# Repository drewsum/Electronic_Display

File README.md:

# Electronic_Display
320x256 LED Display, Marquette Senior Design Project2018-2019, Team E44

20 64x64 HUB75E LED Panels strung together in a 5x4 arrangement, controlled by a PIC32MZ MCU on a host board, alongside an android app

Microconctroller U601 on logic PCB is programmed with firmware in sfw/embedded_firmware/U601_Firmware with PICKIT 3

Two PCBs reside in hdw, designed in KiCad v5.1.0. Both projects require schematic symbols and footprint libraries located in hdw/lib

Embedded firmware resides in sfw/embedded_firmware, built with XC32 v21.0 w/ Pro license (-O2 omptimization level) with MPLabX v5.15

Android app resides in sfw/app/LED_Display, built with Android Studio API level 26

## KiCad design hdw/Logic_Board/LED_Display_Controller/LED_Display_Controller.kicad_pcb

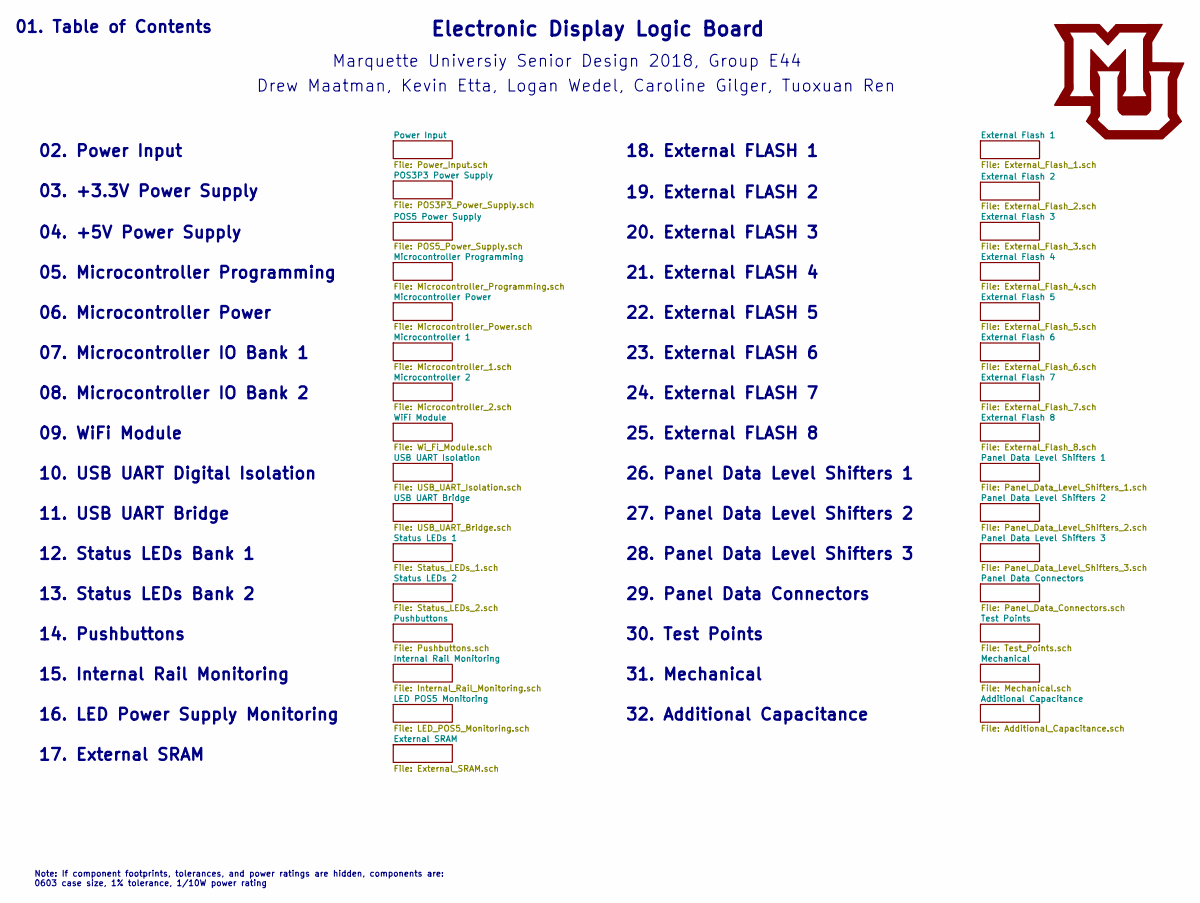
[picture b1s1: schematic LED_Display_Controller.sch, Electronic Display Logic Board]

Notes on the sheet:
02. Power Input
03. +3.3V Power Supply
04. +5V Power Supply
05. Microcontroller Programming
06. Microcontroller Power
07. Microcontroller IO Bank 1
08. Microcontroller IO Bank 2
09. WiFi Module
10. USB UART Digital Isolation
11. USB UART Bridge
12. Status LEDs Bank 1
13. Status LEDs Bank 2
14. Pushbuttons
15. Internal Rail Monitoring
16. LED Power Supply Monitoring
17. External SRAM
18. External FLASH 1
19. External FLASH 2
20. External FLASH 3
21. External FLASH 4
22. External FLASH 5
23. External FLASH 6
24. External FLASH 7
25. External FLASH 8
26. Panel Data Level Shifters 1
27. Panel Data Level Shifters 2
28. Panel Data Level Shifters 3
29. Panel Data Connectors
30. Test Points
31. Mechanical
Electronic Display Logic Board
Marquette Universiy Senior Design 2018, Group E44
Drew Maatman, Kevin Etta, Logan Wedel, Caroline Gilger, Tuoxuan Ren
01. Table of Contents
Note: If component footprints, tolerances, and power ratings are hidden, components are: 0603 case size, 1% tolerance, 1/10W power rating
32. Additional Capacitance

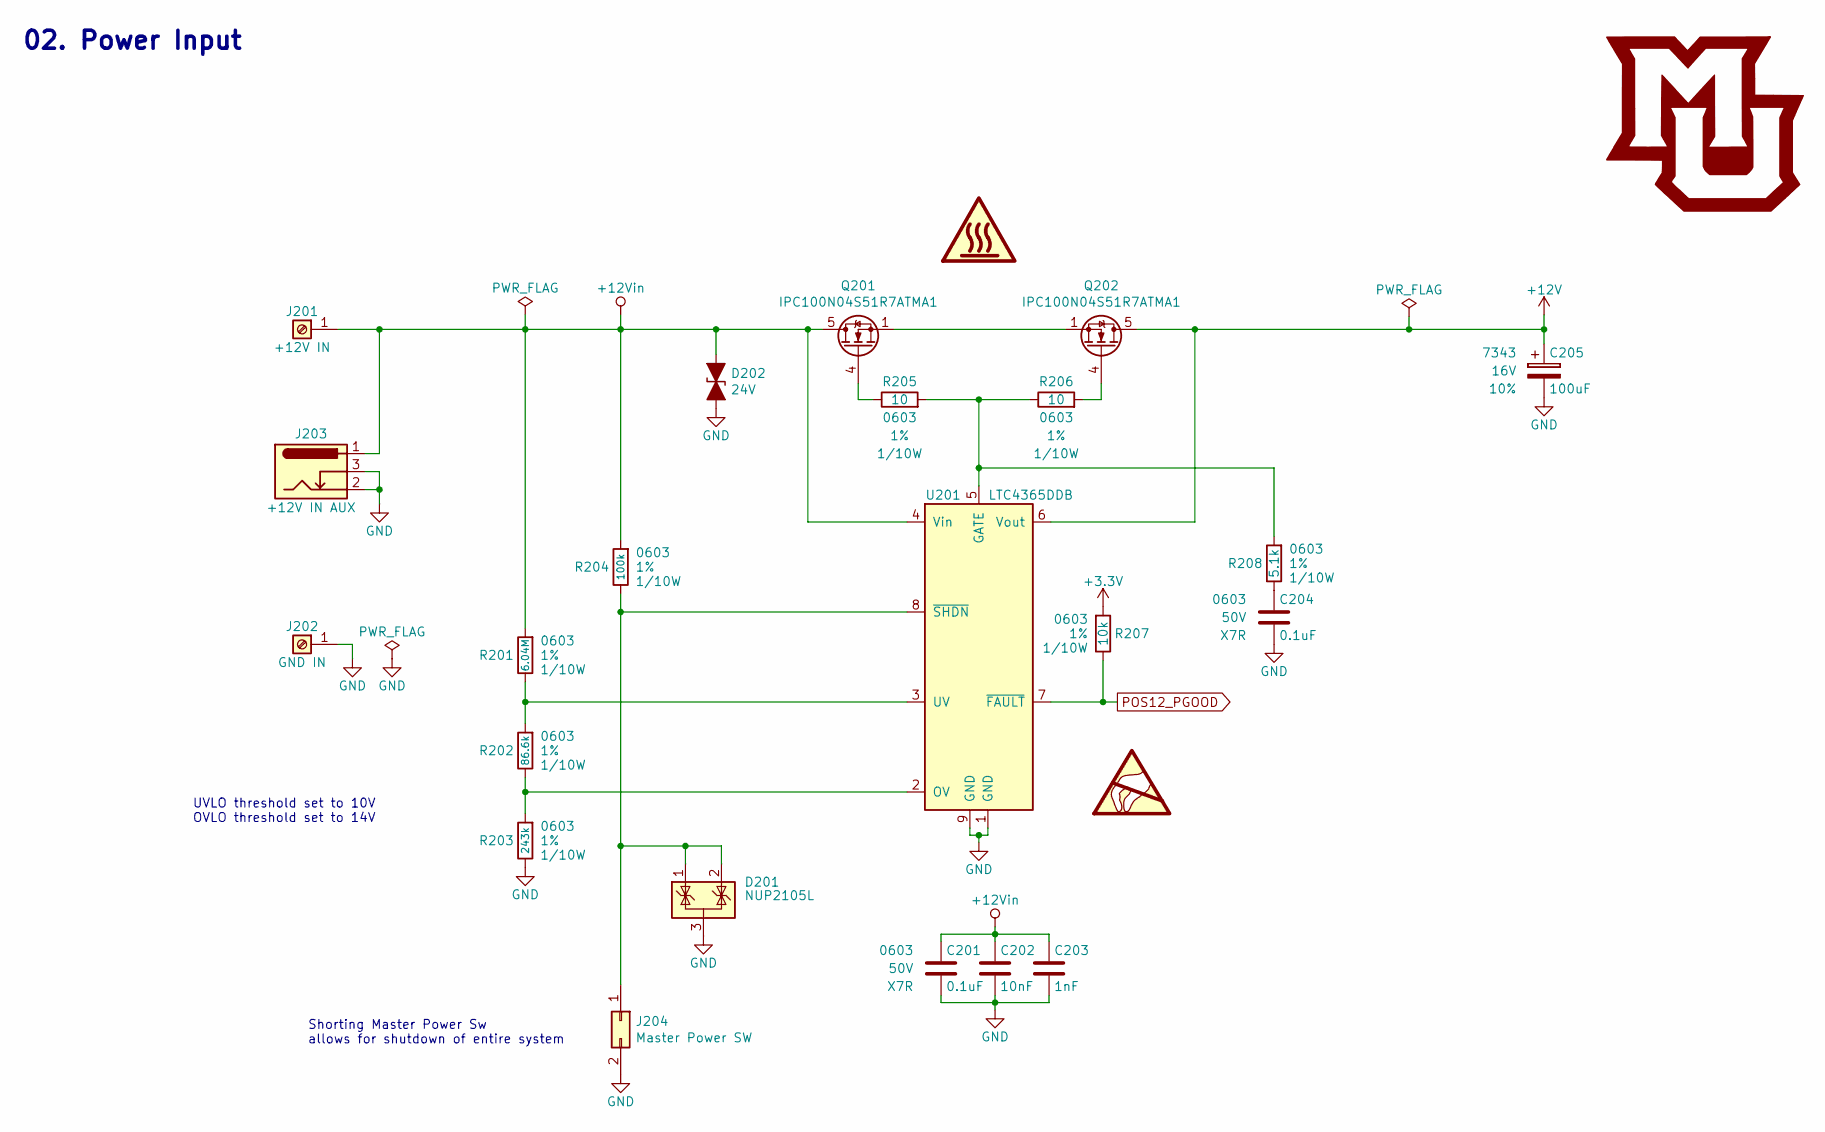
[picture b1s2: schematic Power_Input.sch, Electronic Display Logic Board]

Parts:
C201, C204: 0.1uF; C_0603; Voltage 50V; Digi-Key PN 311-1344-1-ND
C202: 10nF; C_0603; Voltage 50V; Digi-Key PN 1276-1921-1-ND
C203: 1nF; C_0603; Voltage 50V; Digi-Key PN 1276-1018-1-ND
C205: 100uF; CP_Tantalum_Case-X_EIA-7343-43_Reflow; Voltage 16V; Tolerance 10%; Digi-Key PN 718-1102-1-ND
D201: NUP2105L; SOT-23; Digi-Key PN NUP2105LT1GOSCT-ND
D202: 24V; D_SMA; Digi-Key PN SMAJ24CALFCT-ND
J201: +12V IN; Wuerth_7461096_M4_Shank_9pos; Digi-Key PN 732-3214-ND
J202: GND IN; Wuerth_7461096_M4_Shank_9pos; Digi-Key PN 732-3214-ND
J203: +12V IN AUX; BARREL_JACK; Digi-Key PN CP-202BH-ND
J204: Master Power SW; Pin_Header_Straight_1x02_Pitch2.54mm
Q201, Q202: IPC100N04S51R7ATMA1; TDSON-8-1; Digi-Key PN IPC100N04S51R7ATMA1CT-ND
R201: 6.04M; R_0603; Tolerance 1%; Digi-Key PN 541-6.04MHCT-ND
R202: 86.6k; R_0603; Tolerance 1%; Digi-Key PN 311-86.6KHRCT-ND
R203: 243k; R_0603; Tolerance 1%; Digi-Key PN 311-243KHRCT-ND
R204: 100k; R_0603; Tolerance 1%; Digi-Key PN A106046CT-ND
R205, R206: 10; R_0603; Tolerance 1%; Digi-Key PN YAG3351CT-ND
R207: 10k; R_0603; Tolerance 1%; Digi-Key PN RMCF0603FT10K0CT-ND
R208: 5.1k; R_0603; Tolerance 1%; Digi-Key PN YAG3621CT-ND
U201: LTC4365DDB; DFN-8-1EP_2x3mm_Pitch0.5mm; Digi-Key PN LTC4365IDDB#TRMPBFCT-ND

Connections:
+3V3: R207.1; also elsewhere on the board
+12V: C205.1, Q202.5 (D), U201.6 (Vout); also elsewhere on the board
+12Vin: C201.1, C202.1, C203.1, D202.1 (A1), J201.1, J203.1, Q201.5 (D), R201.1, R204.1, U201.4 (Vin); also elsewhere on the board
GND: C201.2, C202.2, C203.2, C204.2, C205.2, D201.3 (A), D202.2 (A2), J202.1, J203.2, J203.3, J204.2, R203.2, U201.1 (GND), U201.9 (GND); also elsewhere on the board
unnamed: C204.1, R208.2
unnamed: D201.1 (K), D201.2 (K), J204.1, R204.2, U201.8 (~SHDN)
unnamed: Q201.1 (S), Q201.2 (S), Q201.3 (S), Q202.1 (S), Q202.2 (S), Q202.3 (S)
unnamed: Q201.4 (G), R205.2
unnamed: Q202.4 (G), R206.1
unnamed: R201.2, R202.1, U201.3 (UV)
unnamed: R202.2, R203.1, U201.2 (OV)
unnamed: R205.1, R206.2, R208.1, U201.5 (GATE)
POS12_PGOOD: R207.2, U201.7 (~FAULT); also elsewhere on the board

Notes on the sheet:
UVLO threshold set to 10V OVLO threshold set to 14V
Shorting Master Power Sw allows for shutdown of entire system
02. Power Input

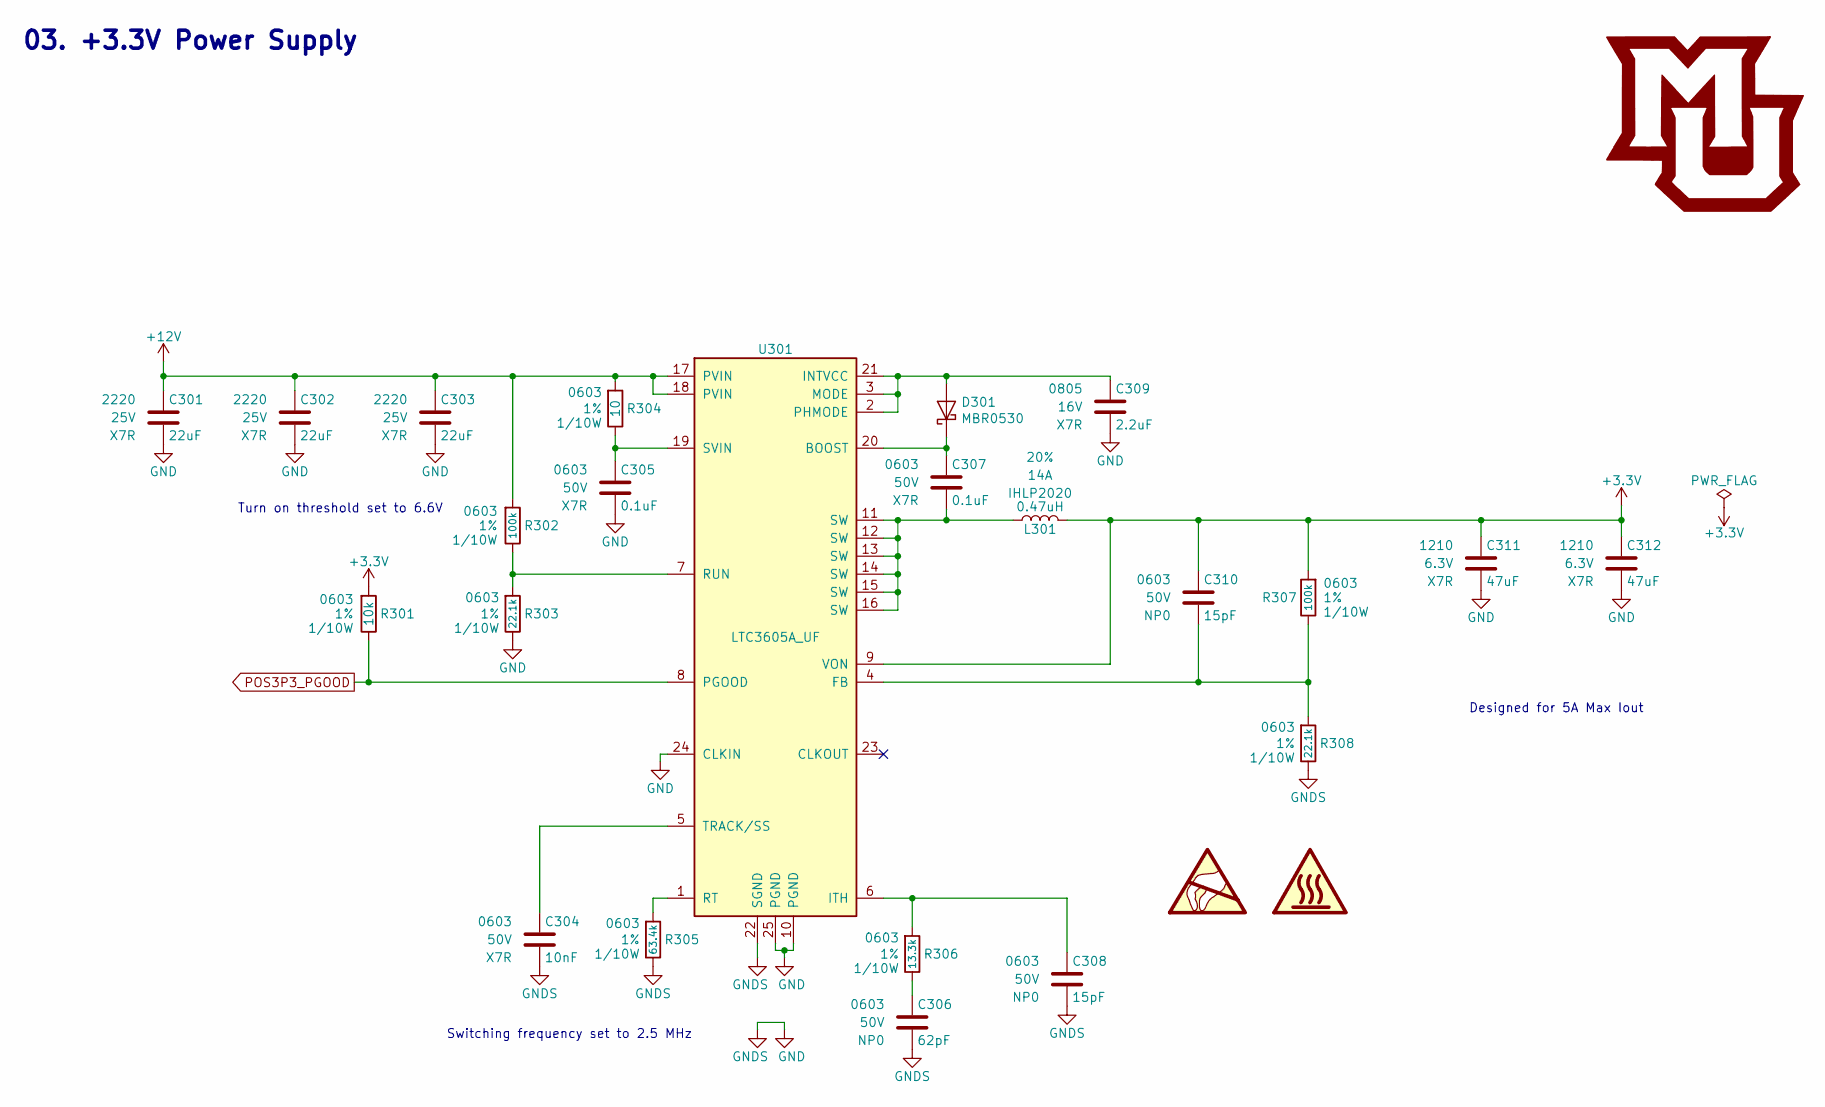
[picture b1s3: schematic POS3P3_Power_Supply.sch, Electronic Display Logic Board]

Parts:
C301, C302, C303: 22uF; C_2220; Voltage 25V; Digi-Key PN 445-1453-1-ND
C304: 10nF; C_0603; Voltage 50V; Digi-Key PN 1276-1921-1-ND
C305, C307: 0.1uF; C_0603; Voltage 50V; Digi-Key PN 311-1344-1-ND
C306: 62pF; C_0603; Voltage 50V; Digi-Key PN 1276-2320-1-ND
C308, C310: 15pF; C_0603; Voltage 50V; Digi-Key PN 478-10289-1-ND
C309: 2.2uF; C_0805; Voltage 16V; Digi-Key PN 445-5691-1-ND
C311, C312: 47uF; C_1210; Voltage 6.3V; Digi-Key PN 490-4844-1-ND
D301: MBR0530; D_SOD-123; Digi-Key PN MBR0530T1GOSCT-ND
L301: 0.47uH; L_Vishay_IHLP-2020; Tolerance 20%; Digi-Key PN 541-1231-1-ND
R301: 10k; R_0603; Tolerance 1%; Digi-Key PN RMCF0603FT10K0CT-ND
R302, R307: 100k; R_0603; Tolerance 1%; Digi-Key PN A106046CT-ND
R303, R308: 22.1k; R_0603; Tolerance 1%; Digi-Key PN P22.1KHCT-ND
R304: 10; R_0603; Tolerance 1%; Digi-Key PN YAG3351CT-ND
R305: 63.4k; R_0603; Tolerance 1%; Digi-Key PN 541-63.4KHCT-ND
R306: 13.3k; R_0603; Tolerance 1%; Digi-Key PN P13.3KHCT-ND
U301: LTC3605A_UF; QFN-24-1EP_4x4mm_Pitch0.5mm; Digi-Key PN LTC3605AIUF#TRPBFCT-ND

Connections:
+3V3: C310.1, C311.1, C312.1, L301.2, R301.1, R307.1, U301.9 (VON); also elsewhere on the board
+12V: C301.1, C302.1, C303.1, R302.1, R304.1, U301.17 (PVIN), U301.18 (PVIN); also elsewhere on the board
GND: C301.2, C302.2, C303.2, C304.2, C305.2, C306.2, C308.2, C309.2, C311.2, C312.2, R303.2, R305.2, R308.2, U301.10 (PGND), U301.22 (SGND), U301.24 (CLKIN), U301.25 (PGND); also elsewhere on the board
unnamed: C304.1, U301.5 (TRACK/SS)
unnamed: C305.1, R304.2, U301.19 (SVIN)
unnamed: C306.1, R306.2
unnamed: C307.1, D301.1 (K), U301.20 (BOOST)
unnamed: C307.2, L301.1, U301.11 (SW), U301.12 (SW), U301.13 (SW), U301.14 (SW), U301.15 (SW), U301.16 (SW)
unnamed: C308.1, R306.1, U301.6 (ITH)
unnamed: C309.1, D301.2 (A), U301.2 (PHMODE), U301.3 (MODE), U301.21 (INTVCC)
unnamed: C310.2, R307.2, R308.1, U301.4 (FB)
unnamed: R302.2, R303.1, U301.7 (RUN)
unnamed: R305.1, U301.1 (RT)
POS3P3_PGOOD: R301.2, U301.8 (PGOOD); also elsewhere on the board

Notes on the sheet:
03. +3.3V Power Supply
Designed for 5A Max Iout
Turn on threshold set to 6.6V
Switching frequency set to 2.5 MHz

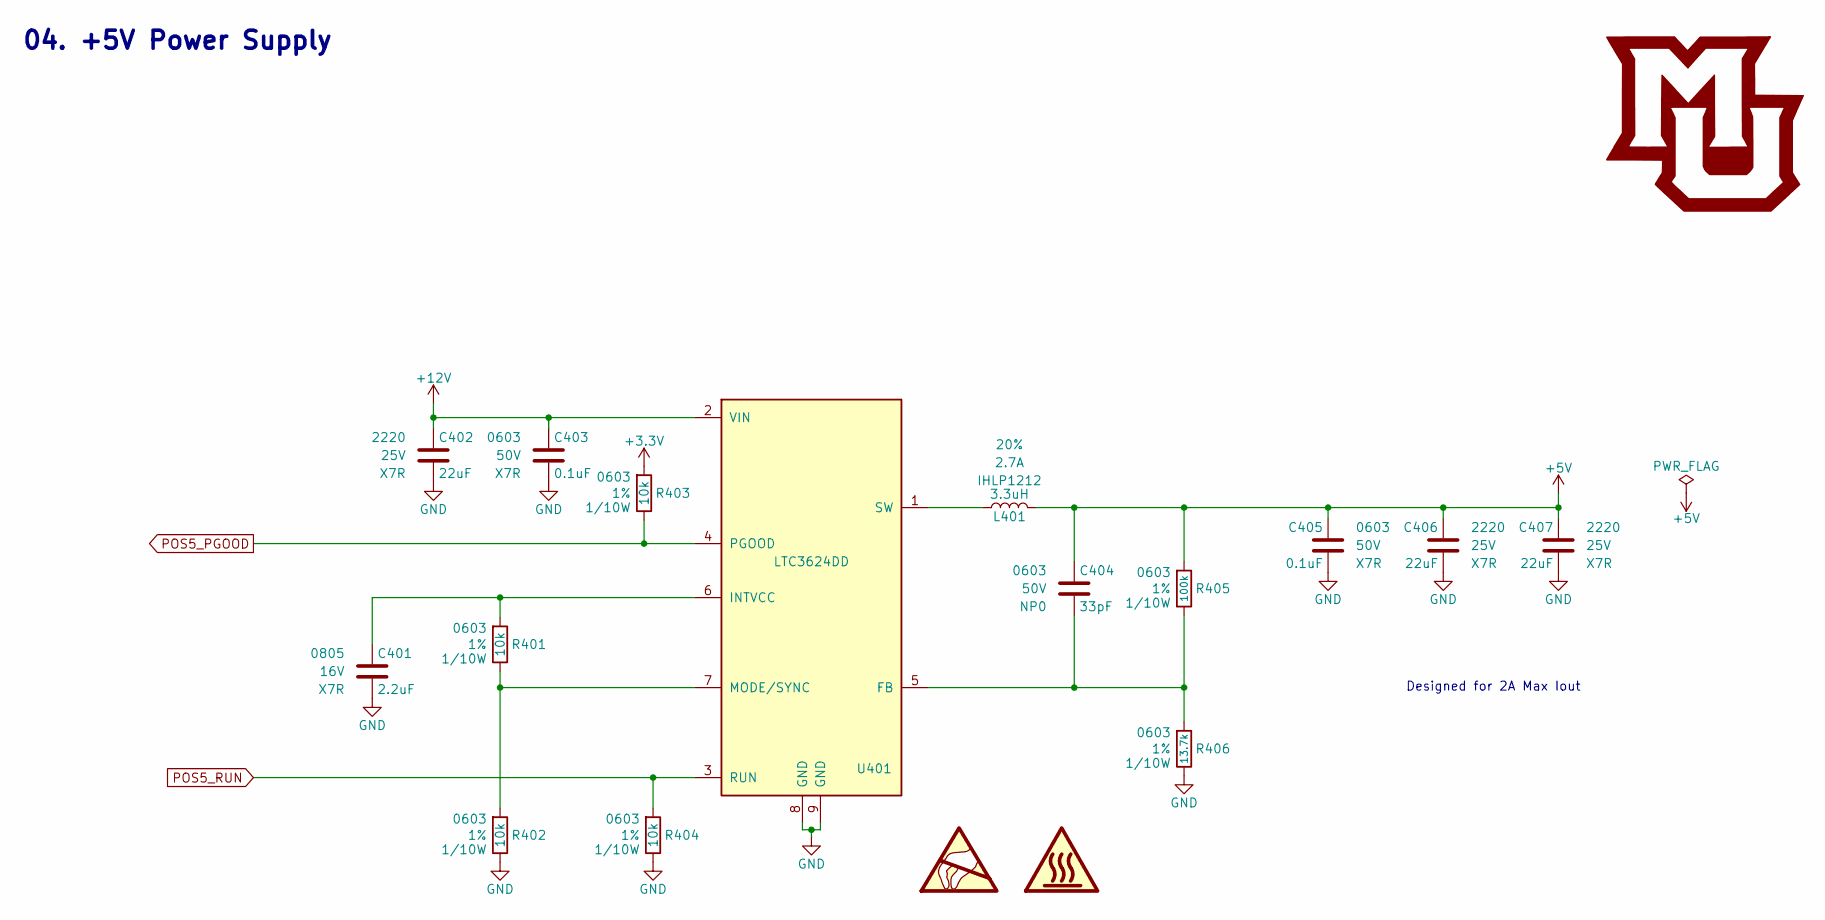
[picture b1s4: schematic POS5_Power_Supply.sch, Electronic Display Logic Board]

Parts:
C401: 2.2uF; C_0805; Voltage 16V; Digi-Key PN 445-5691-1-ND
C402, C406, C407: 22uF; C_2220; Voltage 25V; Digi-Key PN 445-1453-1-ND
C403, C405: 0.1uF; C_0603; Voltage 50V; Digi-Key PN 311-1344-1-ND
C404: 33pF; C_0603; Voltage 50V; Digi-Key PN 399-1055-1-ND
L401: 3.3uH; L_Vishay_IHLP-1212; Tolerance 20%; Digi-Key PN 541-2567-1-ND
R401, R402, R403, R404: 10k; R_0603; Tolerance 1%; Digi-Key PN RMCF0603FT10K0CT-ND
R405: 100k; R_0603; Tolerance 1%; Digi-Key PN A106046CT-ND
R406: 13.7k; R_0603; Tolerance 1%; Digi-Key PN P13.7KHCT-ND
U401: LTC3624DD; DFN-8-1EP_3x3mm_Pitch0.5mm; Digi-Key PN LTC3624IDD#PBF-ND

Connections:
+3V3: R403.1; also elsewhere on the board
+5V: C404.1, C405.1, C406.1, C407.1, L401.2, R405.1; also elsewhere on the board
+12V: C402.1, C403.1, U401.2 (VIN); also elsewhere on the board
GND: C401.2, C402.2, C403.2, C405.2, C406.2, C407.2, R402.2, R404.2, R406.2, U401.8 (GND), U401.9 (GND); also elsewhere on the board
unnamed: C401.1, R401.1, U401.6 (INTVCC)
unnamed: C404.2, R405.2, R406.1, U401.5 (FB)
unnamed: L401.1, U401.1 (SW)
unnamed: R401.2, R402.1, U401.7 (MODE/SYNC)
POS5_PGOOD: R403.2, U401.4 (PGOOD); also elsewhere on the board
POS5_RUN: R404.1, U401.3 (RUN); also elsewhere on the board

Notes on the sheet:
Designed for 2A Max Iout
04. +5V Power Supply

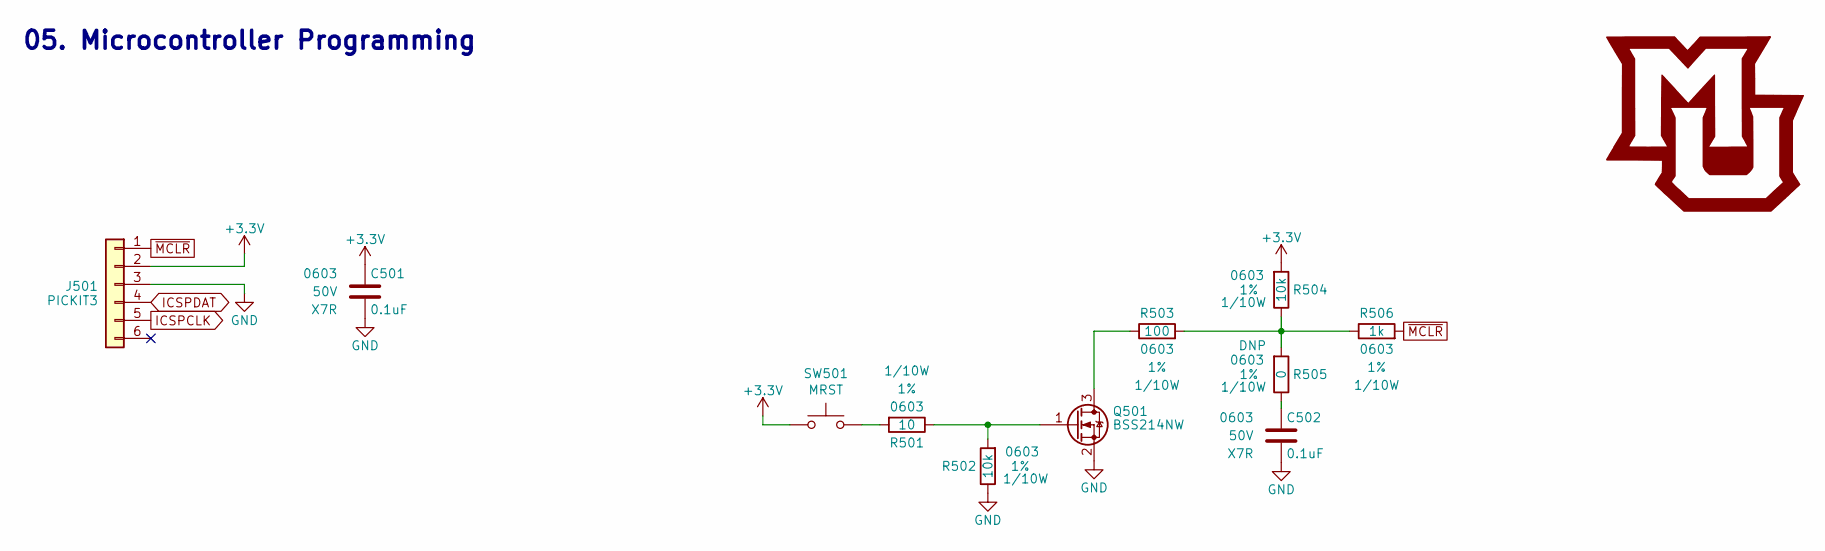
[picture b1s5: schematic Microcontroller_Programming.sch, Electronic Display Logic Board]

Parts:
C501, C502: 0.1uF; C_0603; Voltage 50V; Digi-Key PN 311-1344-1-ND
J501: PICKIT3; PICKIT3_Header
Q501: BSS214NW; SOT-323_SC-70; Digi-Key PN BSS214NWH6327XTSA1CT-ND
R501: 10; R_0603; Tolerance 1%; Digi-Key PN YAG3351CT-ND
R502, R504: 10k; R_0603; Tolerance 1%; Digi-Key PN RMCF0603FT10K0CT-ND
R503: 100; R_0603; Tolerance 1%; Digi-Key PN A106047CT-ND
R505: 0; R_0603; Tolerance 1%; Digi-Key PN 311-0.0GRCT-ND
R506: 1k; R_0603; Tolerance 1%; Digi-Key PN RMCF0603FT1K00CT-ND
SW501: MRST; SW_PUSH_6mm

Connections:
+3V3: C501.1, J501.2, R504.1, SW501.1; also elsewhere on the board
GND: C501.2, C502.2, J501.3, Q501.2 (S), R502.2; also elsewhere on the board
ICSPCLK: J501.5; also elsewhere on the board
ICSPDAT: J501.4; also elsewhere on the board
unnamed: C502.1, R505.2
unnamed: Q501.1 (G), R501.2, R502.1
unnamed: Q501.3 (D), R503.2
unnamed: R501.1, SW501.2
unnamed: R503.1, R504.2, R505.1, R506.2
~MCLR: J501.1, R506.1; also elsewhere on the board

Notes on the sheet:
05. Microcontroller Programming

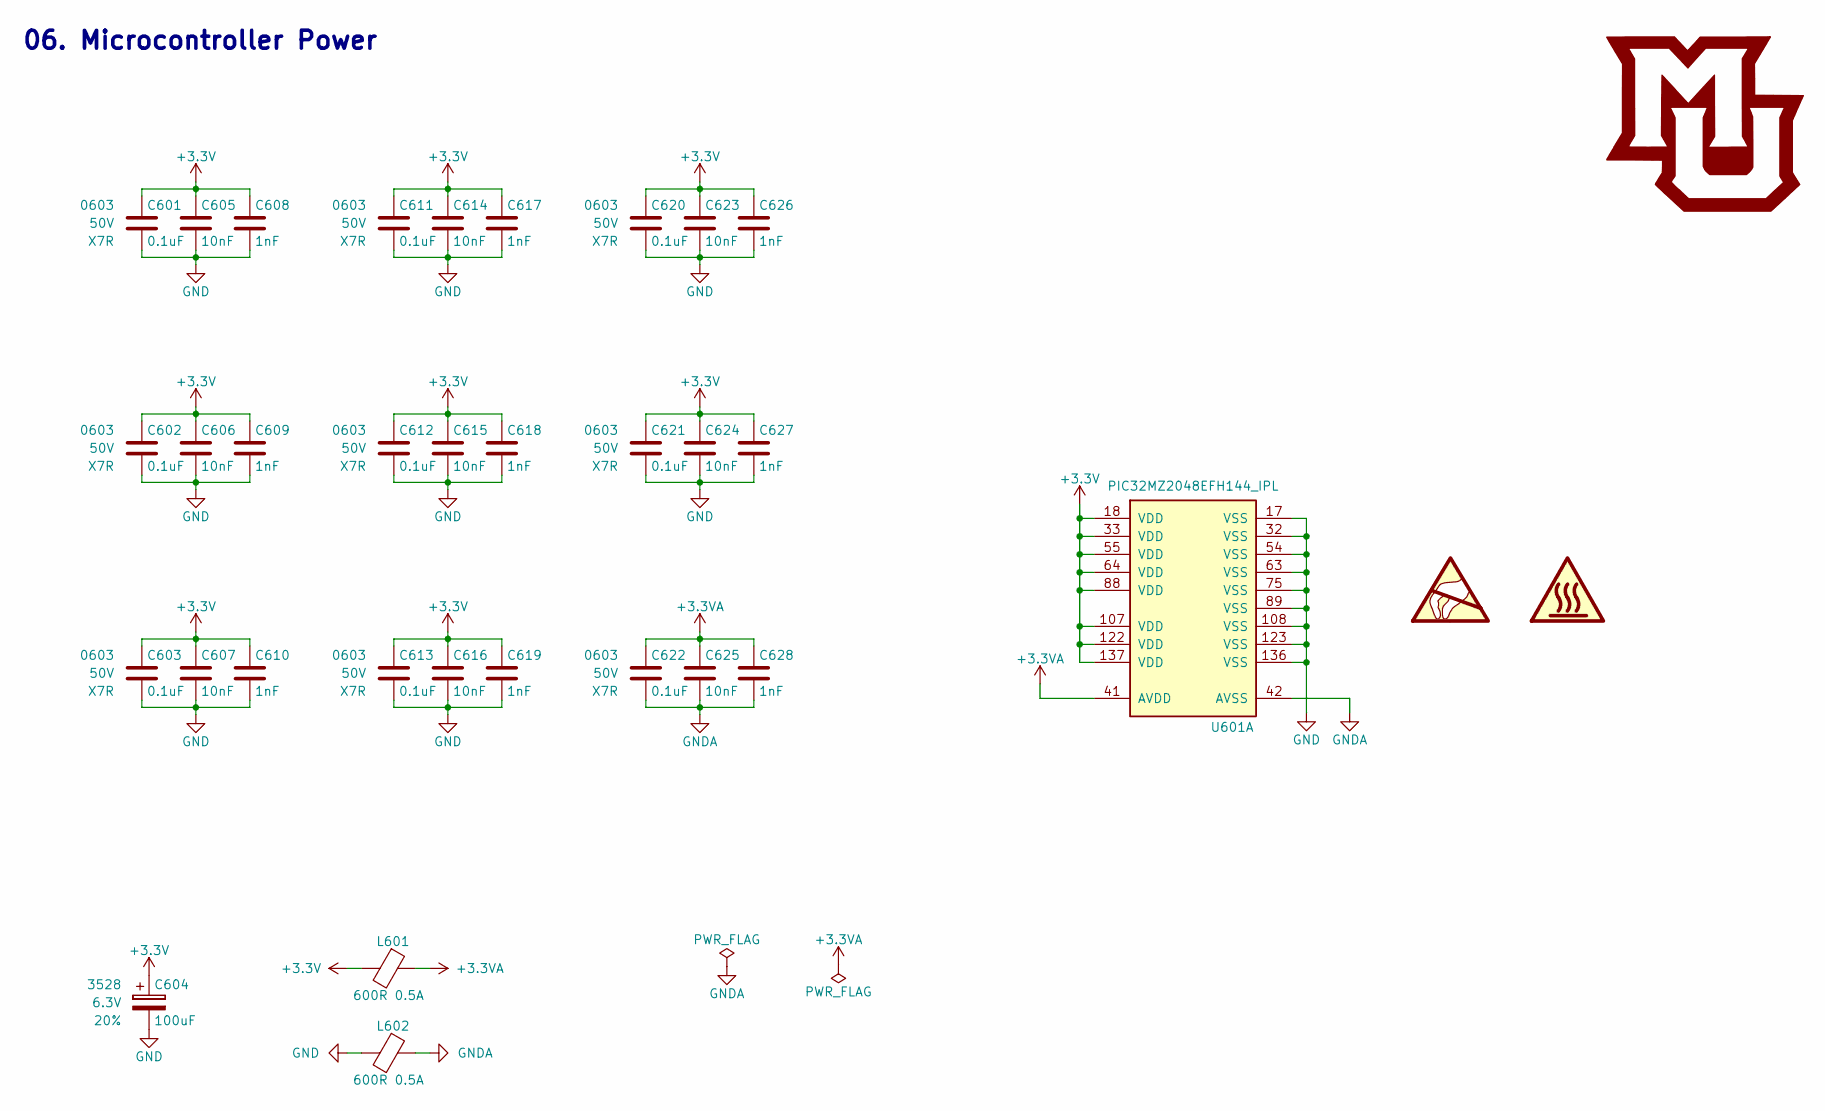
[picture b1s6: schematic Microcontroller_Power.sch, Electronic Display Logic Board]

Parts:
C601, C602, C603, C611, C612, C613, C620, C621, C622: 0.1uF; C_0603; Voltage 50V; Digi-Key PN 311-1344-1-ND
C604: 100uF; CP_Tantalum_Case-B_EIA-3528-21_Reflow; Voltage 6.3V; Tolerance 20%; Digi-Key PN 478-3130-1-ND
C605, C606, C607, C614, C615, C616, C623, C624, C625: 10nF; C_0603; Voltage 50V; Digi-Key PN 1276-1921-1-ND
C608, C609, C610, C617, C618, C619, C626, C627, C628: 1nF; C_0603; Voltage 50V; Digi-Key PN 1276-1018-1-ND
L601, L602: 600R 0.5A; L_0603; Digi-Key PN 732-2389-1-ND
U601: PIC32MZ2048EFH144_IPL; TQFP-144_20x20mm_Pitch0.5mm; Digi-Key PN PIC32MZ2048EFH144-I/PL-ND

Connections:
+3.3VA: C622.1, C625.1, C628.1, L601.1, U601.41 (AVDD)
+3V3: C601.1, C602.1, C603.1, C604.1, C605.1, C606.1, C607.1, C608.1, C609.1, C610.1, C611.1, C612.1, C613.1, C614.1, C615.1, C616.1, C617.1, C618.1, C619.1, C620.1, C621.1, C623.1, C624.1, C626.1, C627.1, L601.2, U601.18 (VDD), U601.33 (VDD), U601.55 (VDD), U601.64 (VDD), U601.88 (VDD), U601.107 (VDD), U601.122 (VDD), U601.137 (VDD); also elsewhere on the board
GND: C601.2, C602.2, C603.2, C604.2, C605.2, C606.2, C607.2, C608.2, C609.2, C610.2, C611.2, C612.2, C613.2, C614.2, C615.2, C616.2, C617.2, C618.2, C619.2, C620.2, C621.2, C623.2, C624.2, C626.2, C627.2, L602.2, U601.17 (VSS), U601.32 (VSS), U601.54 (VSS), U601.63 (VSS), U601.75 (VSS), U601.89 (VSS), U601.108 (VSS), U601.123 (VSS), U601.136 (VSS); also elsewhere on the board
GNDA: C622.2, C625.2, C628.2, L602.1, U601.42 (AVSS)

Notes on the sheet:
06. Microcontroller Power

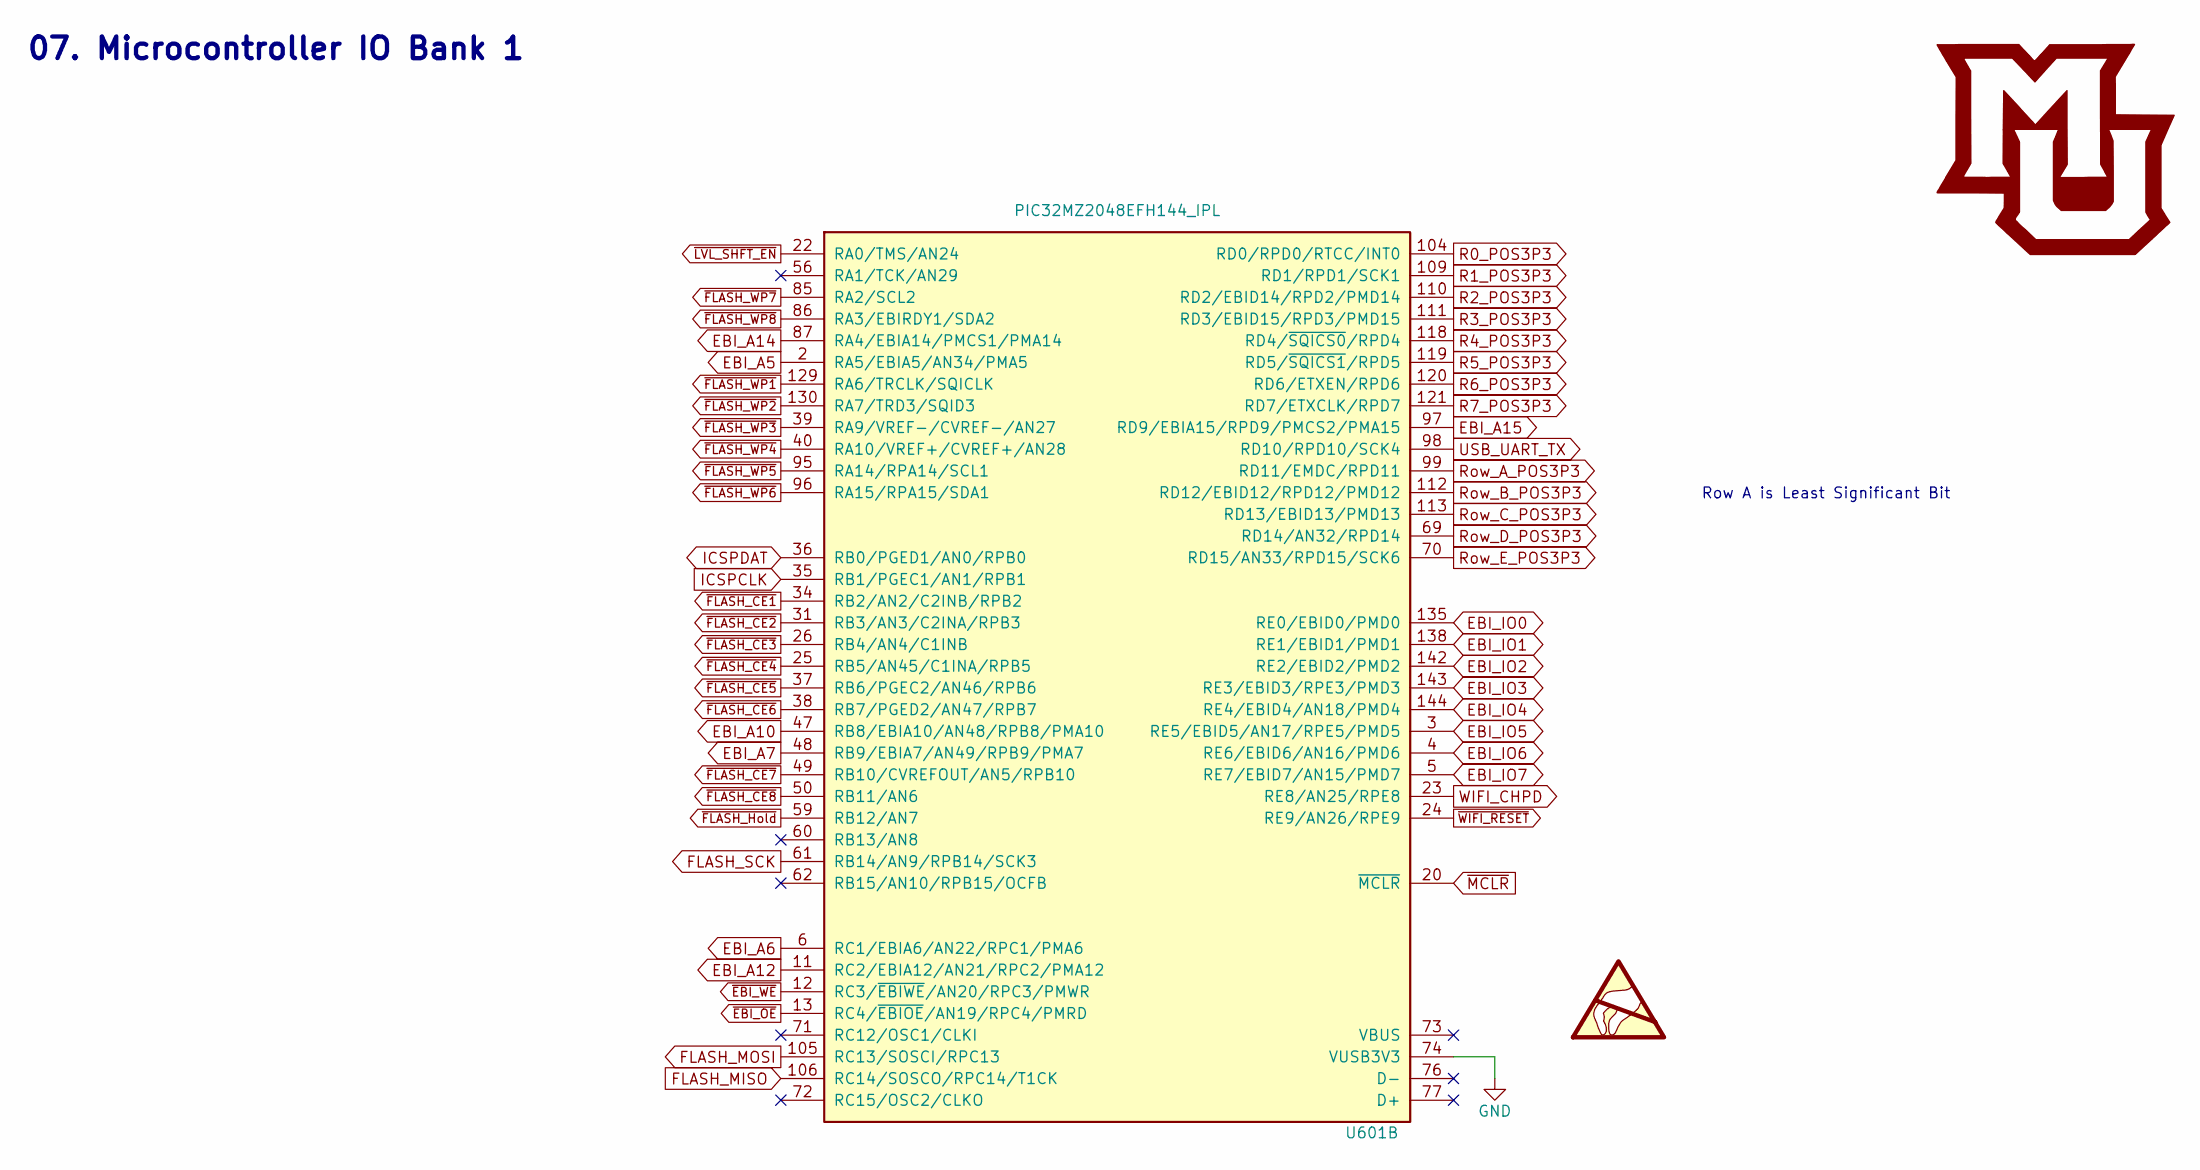
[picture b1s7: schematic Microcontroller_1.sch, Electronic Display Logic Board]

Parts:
U601: PIC32MZ2048EFH144_IPL; TQFP-144_20x20mm_Pitch0.5mm; Digi-Key PN PIC32MZ2048EFH144-I/PL-ND

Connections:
EBI_A5: U601.2 (RA5/EBIA5/AN34/PMA5); also elsewhere on the board
EBI_A6: U601.6 (RC1/EBIA6/AN22/RPC1/PMA6); also elsewhere on the board
EBI_A7: U601.48 (RB9/EBIA7/AN49/RPB9/PMA7); also elsewhere on the board
EBI_A10: U601.47 (RB8/EBIA10/AN48/RPB8/PMA10); also elsewhere on the board
EBI_A12: U601.11 (RC2/EBIA12/AN21/RPC2/PMA12); also elsewhere on the board
EBI_A14: U601.87 (RA4/EBIA14/PMCS1/PMA14); also elsewhere on the board
EBI_A15: U601.97 (RD9/EBIA15/RPD9/PMCS2/PMA15); also elsewhere on the board
EBI_IO0: U601.135 (RE0/EBID0/PMD0); also elsewhere on the board
EBI_IO1: U601.138 (RE1/EBID1/PMD1); also elsewhere on the board
EBI_IO2: U601.142 (RE2/EBID2/PMD2); also elsewhere on the board
EBI_IO3: U601.143 (RE3/EBID3/RPE3/PMD3); also elsewhere on the board
EBI_IO4: U601.144 (RE4/EBID4/AN18/PMD4); also elsewhere on the board
EBI_IO5: U601.3 (RE5/EBID5/AN17/RPE5/PMD5); also elsewhere on the board
EBI_IO6: U601.4 (RE6/EBID6/AN16/PMD6); also elsewhere on the board
EBI_IO7: U601.5 (RE7/EBID7/AN15/PMD7); also elsewhere on the board
FLASH_MISO: U601.106 (RC14/SOSCO/RPC14/T1CK); also elsewhere on the board
FLASH_MOSI: U601.105 (RC13/SOSCI/RPC13); also elsewhere on the board
FLASH_SCK: U601.61 (RB14/AN9/RPB14/SCK3); also elsewhere on the board
GND: U601.74 (VUSB3V3); also elsewhere on the board
ICSPCLK: U601.35 (RB1/PGEC1/AN1/RPB1); also elsewhere on the board
ICSPDAT: U601.36 (RB0/PGED1/AN0/RPB0); also elsewhere on the board
R0_POS3P3: U601.104 (RD0/RPD0/RTCC/INT0); also elsewhere on the board
R1_POS3P3: U601.109 (RD1/RPD1/SCK1); also elsewhere on the board
R2_POS3P3: U601.110 (RD2/EBID14/RPD2/PMD14); also elsewhere on the board
R3_POS3P3: U601.111 (RD3/EBID15/RPD3/PMD15); also elsewhere on the board
R4_POS3P3: U601.118 (RD4/~SQICS0~/RPD4); also elsewhere on the board
R5_POS3P3: U601.119 (RD5/~SQICS1~/RPD5); also elsewhere on the board
R6_POS3P3: U601.120 (RD6/ETXEN/RPD6); also elsewhere on the board
R7_POS3P3: U601.121 (RD7/ETXCLK/RPD7); also elsewhere on the board
Row_A_POS3P3: U601.99 (RD11/EMDC/RPD11); also elsewhere on the board
Row_B_POS3P3: U601.112 (RD12/EBID12/RPD12/PMD12); also elsewhere on the board
Row_C_POS3P3: U601.113 (RD13/EBID13/PMD13); also elsewhere on the board
Row_D_POS3P3: U601.69 (RD14/AN32/RPD14); also elsewhere on the board
Row_E_POS3P3: U601.70 (RD15/AN33/RPD15/SCK6); also elsewhere on the board
USB_UART_TX: U601.98 (RD10/RPD10/SCK4); also elsewhere on the board
WIFI_CHPD: U601.23 (RE8/AN25/RPE8); also elsewhere on the board
~EBI_OE: U601.13 (RC4/~EBIOE~/AN19/RPC4/PMRD); also elsewhere on the board
~EBI_WE: U601.12 (RC3/~EBIWE~/AN20/RPC3/PMWR); also elsewhere on the board
~FLASH_CE1: U601.34 (RB2/AN2/C2INB/RPB2); also elsewhere on the board
~FLASH_CE2: U601.31 (RB3/AN3/C2INA/RPB3); also elsewhere on the board
~FLASH_CE3: U601.26 (RB4/AN4/C1INB); also elsewhere on the board
~FLASH_CE4: U601.25 (RB5/AN45/C1INA/RPB5); also elsewhere on the board
~FLASH_CE5: U601.37 (RB6/PGEC2/AN46/RPB6); also elsewhere on the board
~FLASH_CE6: U601.38 (RB7/PGED2/AN47/RPB7); also elsewhere on the board
~FLASH_CE7: U601.49 (RB10/CVREFOUT/AN5/RPB10); also elsewhere on the board
~FLASH_CE8: U601.50 (RB11/AN6); also elsewhere on the board
~FLASH_Hold: U601.59 (RB12/AN7); also elsewhere on the board
~FLASH_WP1: U601.129 (RA6/TRCLK/SQICLK); also elsewhere on the board
~FLASH_WP2: U601.130 (RA7/TRD3/SQID3); also elsewhere on the board
~FLASH_WP3: U601.39 (RA9/VREF-/CVREF-/AN27); also elsewhere on the board
~FLASH_WP4: U601.40 (RA10/VREF+/CVREF+/AN28); also elsewhere on the board
~FLASH_WP5: U601.95 (RA14/RPA14/SCL1); also elsewhere on the board
~FLASH_WP6: U601.96 (RA15/RPA15/SDA1); also elsewhere on the board
~FLASH_WP7: U601.85 (RA2/SCL2); also elsewhere on the board
~FLASH_WP8: U601.86 (RA3/EBIRDY1/SDA2); also elsewhere on the board
~LVL_SHFT_EN: U601.22 (RA0/TMS/AN24); also elsewhere on the board
~MCLR: U601.20 (~MCLR~); also elsewhere on the board
~WIFI_RESET: U601.24 (RE9/AN26/RPE9); also elsewhere on the board

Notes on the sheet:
07. Microcontroller IO Bank 1
Row A is Least Significant Bit
